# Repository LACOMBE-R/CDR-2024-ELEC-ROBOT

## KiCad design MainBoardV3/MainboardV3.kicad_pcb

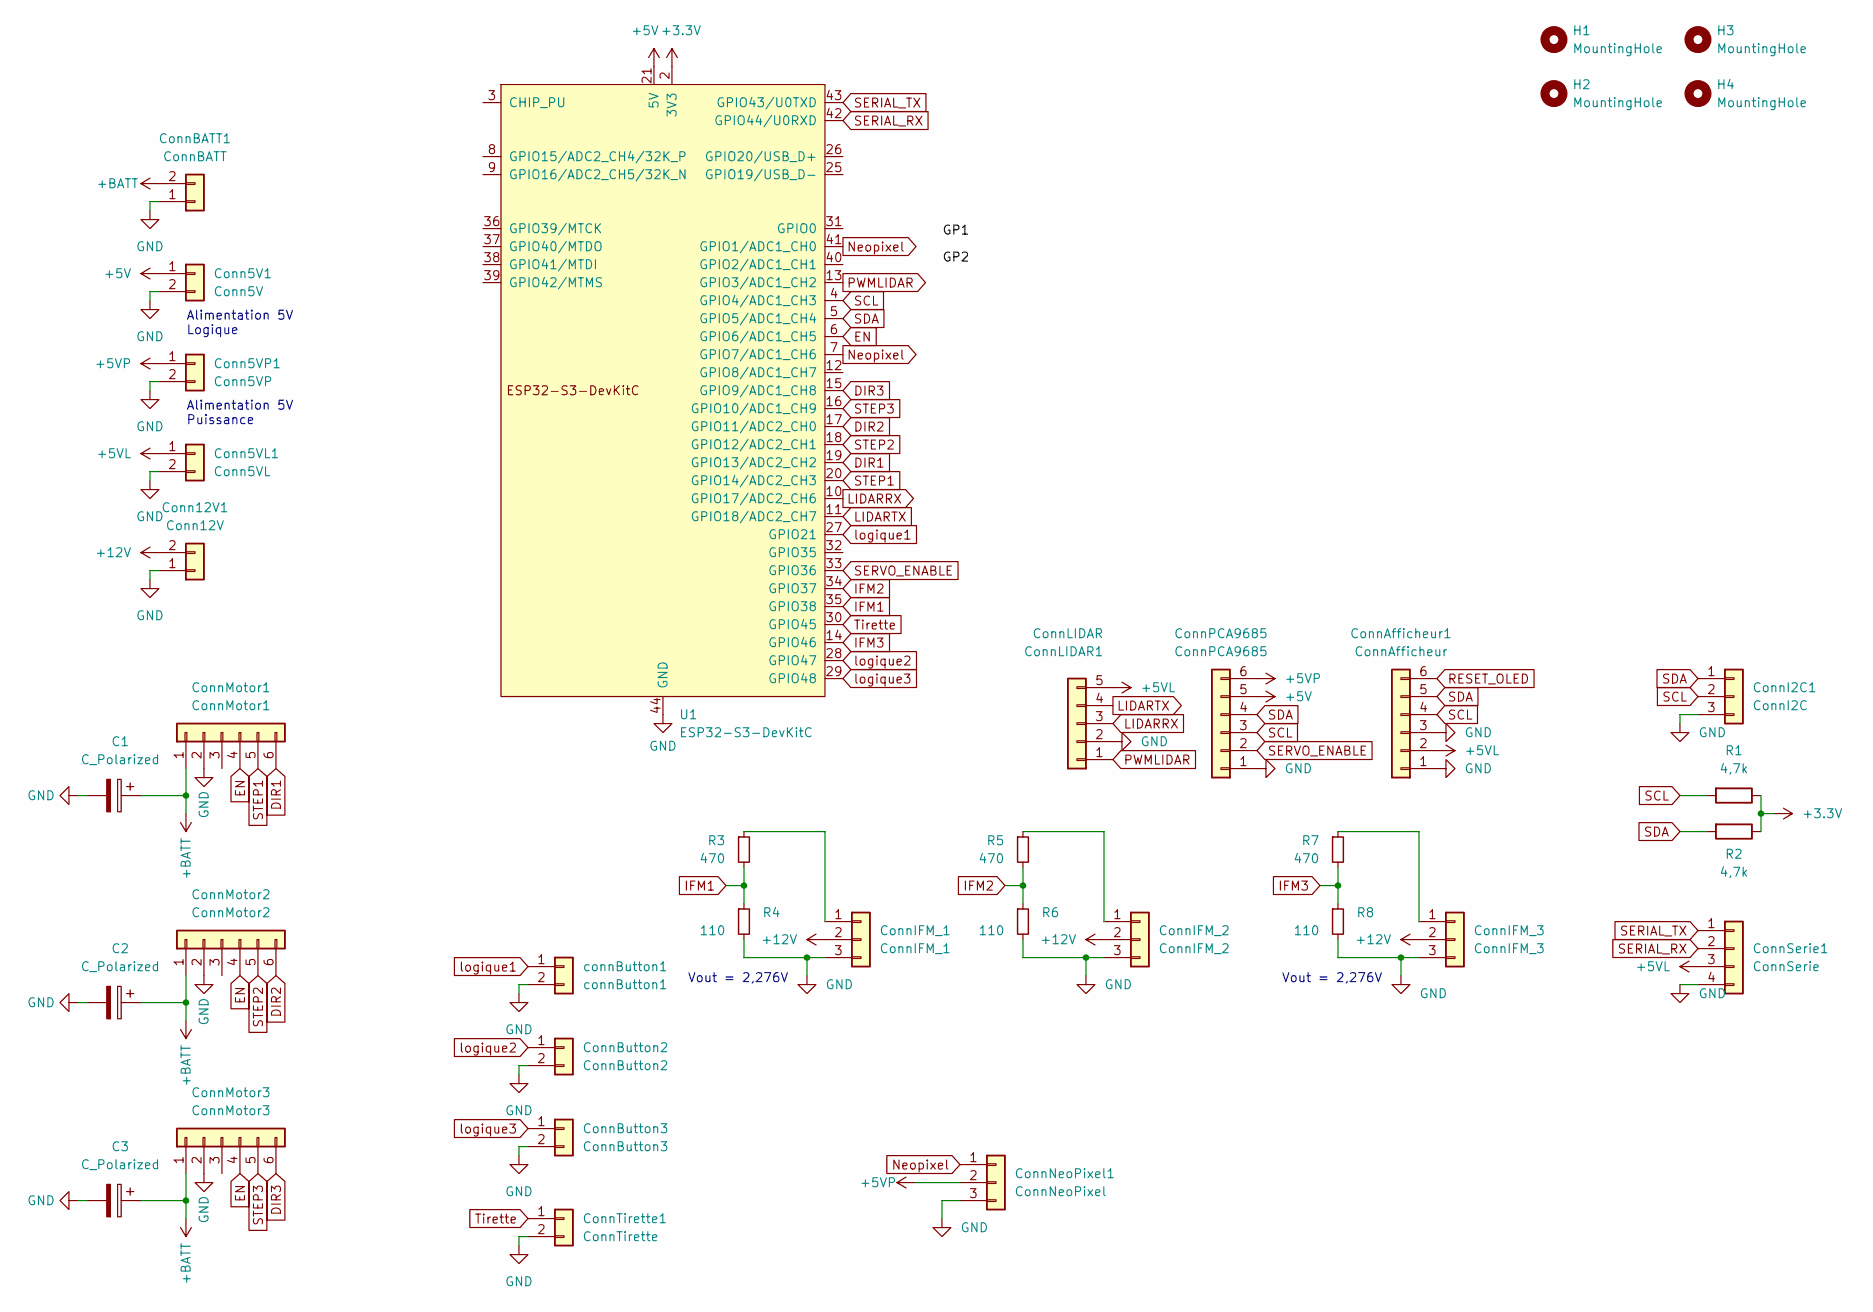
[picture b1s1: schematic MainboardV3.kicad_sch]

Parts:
C1, C2, C3: C_Polarized; CP_Radial_D8.0mm_P3.50mm
Conn5V1: Conn5V; Molex_KK-254_AE-6410-02A_1x02_P2.54mm_Vertical
Conn5VL1: Conn5VL; Molex_KK-254_AE-6410-02A_1x02_P2.54mm_Vertical
Conn5VP1: Conn5VP; Molex_KK-396_A-41791-0002_1x02_P3.96mm_Vertical
Conn12V1: Conn12V; AMASS_XT30U-F_1x02_P5.0mm_Vertical
ConnAfficheur1: ConnAfficheur; JST_EH_B6B-EH-A_1x06_P2.50mm_Vertical
ConnBATT1: ConnBATT; AMASS_XT60-F_1x02_P7.20mm_Vertical
ConnButton2: ConnButton2; Molex_KK-254_AE-6410-02A_1x02_P2.54mm_Vertical
ConnButton3: ConnButton3; Molex_KK-254_AE-6410-02A_1x02_P2.54mm_Vertical
ConnI2C1: ConnI2C; Molex_KK-254_AE-6410-03A_1x03_P2.54mm_Vertical
ConnIFM_1: ConnIFM_1; Molex_KK-254_AE-6410-03A_1x03_P2.54mm_Vertical
ConnIFM_2: ConnIFM_2; Molex_KK-254_AE-6410-03A_1x03_P2.54mm_Vertical
ConnIFM_3: ConnIFM_3; Molex_KK-254_AE-6410-03A_1x03_P2.54mm_Vertical
ConnLIDAR1: ConnLIDAR; JST_EH_B5B-EH-A_1x05_P2.50mm_Vertical
ConnMotor1: ConnMotor1; JST_EH_B6B-EH-A_1x06_P2.50mm_Vertical
ConnMotor2: ConnMotor2; JST_EH_B6B-EH-A_1x06_P2.50mm_Vertical
ConnMotor3: ConnMotor3; JST_EH_B6B-EH-A_1x06_P2.50mm_Vertical
ConnNeoPixel1: ConnNeoPixel; Molex_KK-254_AE-6410-03A_1x03_P2.54mm_Vertical
ConnPCA9685: ConnPCA9685; JST_EH_B6B-EH-A_1x06_P2.50mm_Vertical
ConnSerie1: ConnSerie; JST_EH_B4B-EH-A_1x04_P2.50mm_Vertical
ConnTirette1: ConnTirette; Molex_KK-254_AE-6410-02A_1x02_P2.54mm_Vertical
H1, H2, H3, H4: MountingHole; MountingHole_3.2mm_M3
R1, R2: 4,7k; R_1206_3216Metric_Pad1.30x1.75mm_HandSolder
R3, R5, R7: 470; R_1206_3216Metric_Pad1.30x1.75mm_HandSolder
R4, R6, R8: 110; R_1206_3216Metric_Pad1.30x1.75mm_HandSolder
U1: ESP32-S3-DevKitC
connButton1: connButton1; Molex_KK-254_AE-6410-02A_1x02_P2.54mm_Vertical

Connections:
+3.3V: R1.1, R2.1, U1.1 (3V3), U1.2 (3V3)
+5V: Conn5V1.1, ConnPCA9685.5, U1.21 (5V)
+5VL: Conn5VL1.1, ConnAfficheur1.2, ConnLIDAR1.5, ConnSerie1.3
+5VP: Conn5VP1.1, ConnNeoPixel1.2, ConnPCA9685.6
+12V: Conn12V1.2, ConnIFM_1.2, ConnIFM_2.2, ConnIFM_3.2
+BATT: C1.1, C2.1, C3.1, ConnBATT1.2, ConnMotor1.1, ConnMotor2.1, ConnMotor3.1
DIR1: ConnMotor1.6, U1.19 (GPIO13/ADC2_CH2)
DIR2: ConnMotor2.6, U1.17 (GPIO11/ADC2_CH0)
DIR3: ConnMotor3.6, U1.15 (GPIO9/ADC1_CH8)
EN: ConnMotor1.4, ConnMotor2.4, ConnMotor3.4, U1.6 (GPIO6/ADC1_CH5)
GND: C1.2, C2.2, C3.2, Conn5V1.2, Conn5VL1.2, Conn5VP1.2, Conn12V1.1, ConnAfficheur1.1, ConnAfficheur1.3, ConnBATT1.1, ConnButton2.2, ConnButton3.2, ConnI2C1.3, ConnIFM_1.3, ConnIFM_2.3, ConnIFM_3.3, ConnLIDAR1.2, ConnMotor1.2, ConnMotor2.2, ConnMotor3.2, ConnNeoPixel1.3, ConnPCA9685.1, ConnSerie1.4, ConnTirette1.2, R4.2, R6.2, R8.2, U1.22 (GND), U1.23 (GND), U1.24 (GND), U1.44 (GND), connButton1.2
IFM1: R3.2, R4.1, U1.35 (GPIO38)
IFM2: R5.2, R6.1, U1.34 (GPIO37)
IFM3: R7.2, R8.1, U1.14 (GPIO46)
LIDARRX: ConnLIDAR1.3, U1.10 (GPIO17/ADC2_CH6)
LIDARTX: ConnLIDAR1.4, U1.11 (GPIO18/ADC2_CH7)
Neopixel: ConnNeoPixel1.1, U1.7 (GPIO7/ADC1_CH6), U1.41 (GPIO1/ADC1_CH0)
unnamed: ConnIFM_1.1, R3.1
unnamed: ConnIFM_2.1, R5.1
unnamed: ConnIFM_3.1, R7.1
PWMLIDAR: ConnLIDAR1.1, U1.13 (GPIO3/ADC1_CH2)
RESET_OLED: ConnAfficheur1.6
SCL: ConnAfficheur1.4, ConnI2C1.2, ConnPCA9685.3, R1.2, U1.4 (GPIO4/ADC1_CH3)
SDA: ConnAfficheur1.5, ConnI2C1.1, ConnPCA9685.4, R2.2, U1.5 (GPIO5/ADC1_CH4)
SERIAL_RX: ConnSerie1.2, U1.42 (GPIO44/U0RXD)
SERIAL_TX: ConnSerie1.1, U1.43 (GPIO43/U0TXD)
SERVO_ENABLE: ConnPCA9685.2, U1.33 (GPIO36)
STEP1: ConnMotor1.5, U1.20 (GPIO14/ADC2_CH3)
STEP2: ConnMotor2.5, U1.18 (GPIO12/ADC2_CH1)
STEP3: ConnMotor3.5, U1.16 (GPIO10/ADC1_CH9)
Tirette: ConnTirette1.1, U1.30 (GPIO45)
logique1: U1.27 (GPIO21), connButton1.1
logique2: ConnButton2.1, U1.28 (GPIO47)
logique3: ConnButton3.1, U1.29 (GPIO48)

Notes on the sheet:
Vout = 2,276V
Alimentation 5V Puissance
Alimentation 5V Logique

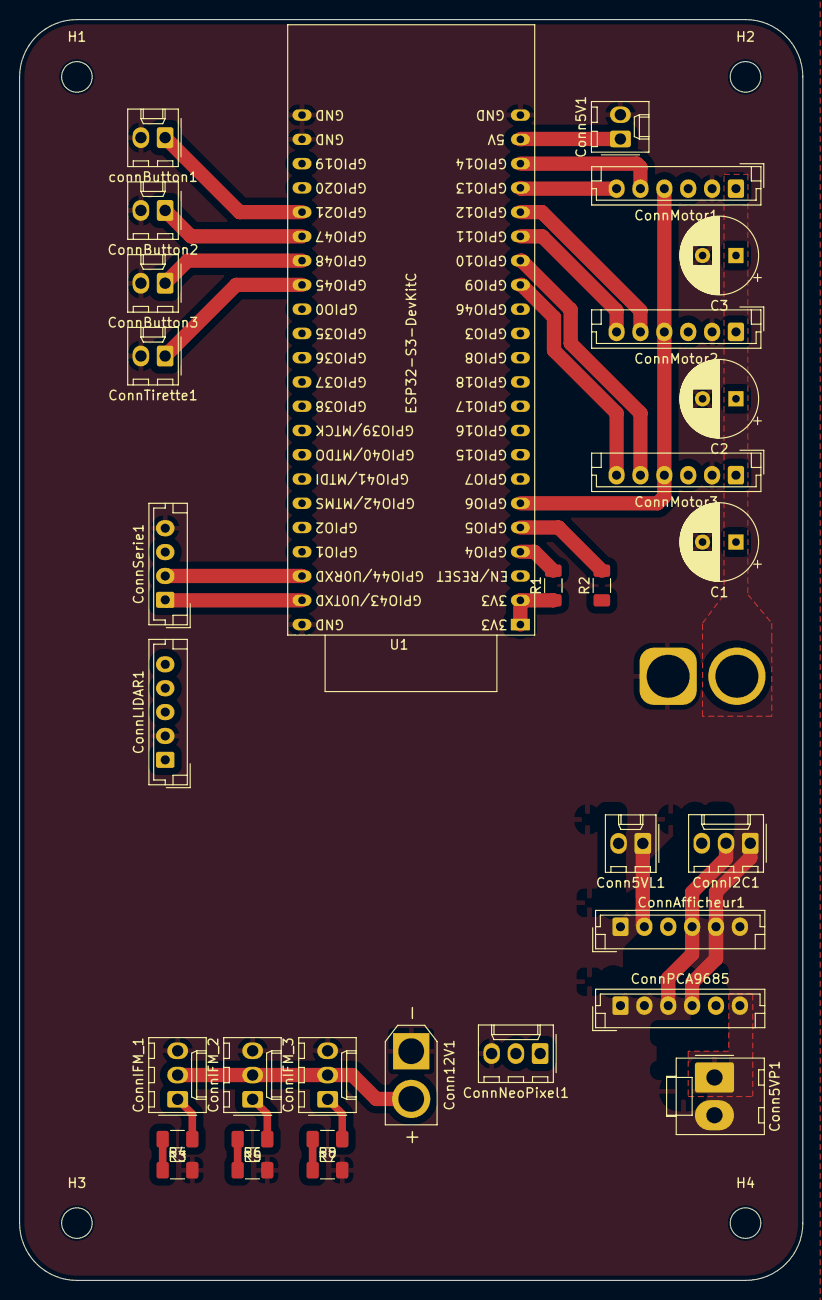
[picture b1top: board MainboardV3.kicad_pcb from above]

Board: 2 copper layers, 82.0 x 132.0 mm, 37 parts (1 on the bottom side), 33 nets.

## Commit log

2023-11-22 Modified to suit needs
2023-11-24 Adapted schematic to existing needs
2023-12-07 Modified board
